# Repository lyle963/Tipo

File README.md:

# Tipo
Plug n Play Braille Keyboard for your smartphone

# What is available?
1. Arduino Firmware for a USB keyboard using atmega32u4
2. Eagle CAD board files to print the PCB

# TO-DO
1. Remove bt ezkey module and get the arduino micro to type stuff onto notepad using 2 or 3 buttons - Done

2. Repeat with USBOTG and make sure phone responds - Done

3. Connect 8 keys to micro on breadboard in matrix or parallel layout to verify all peri electronics - Done

4. Dump Leonardo bootloader to wild Atmega32u4 Chip - Done

5. Breadboard standalone chip with external oscillator,caps,resistors etc - Skipped like a bawz

6. Design / Fab pcb and test with phone - Done

7. CAD Case

8. Print case

9. Give board to visually impared peeps & get feedback

10. Brailler Trainer app

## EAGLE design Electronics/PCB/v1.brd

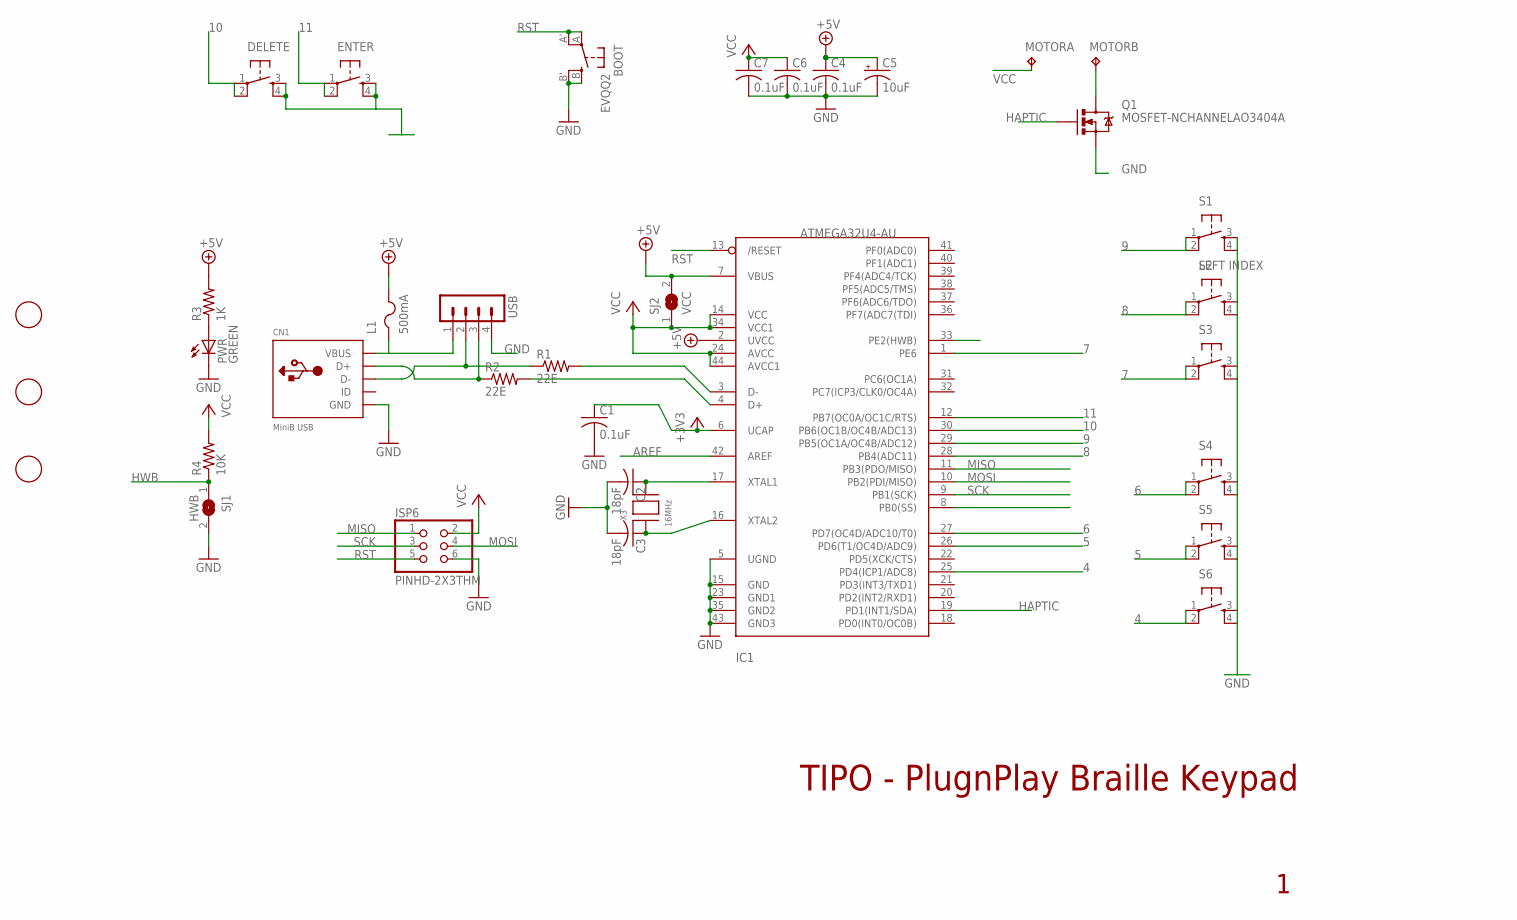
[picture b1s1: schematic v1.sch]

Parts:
BOOT: EVQQ2; EVQ-Q2
C1, C4, C6, C7: 0.1uF; C0805K
C2, C3: 18pF; C0805K
C5: 10uF; A/3216-18R
CN1: MiniB USB; USB-MINIB
DELETE: TAC_SWITCHPTH; TACTILE-PTH
ENTER: TAC_SWITCHPTH; TACTILE-PTH
IC1: ATMEGA32U4-AU; TQFP44
ISP6: PINHD-2X3THM; ISP6
L1: 500mA; R1206
MOTOR: TP2P2-38-17; P2-38-17
PWR: GREEN; CHIPLED_0805
Q1: MOSFET-NCHANNELAO3404A; SOT23-3
R1, R2: 22E; R0805
R3: 1K; R0805
R4: 10K; R0805
S1: LEFT INDEX; TACTILE-PTH
S2, S3, S4, S5, S6: TAC_SWITCHPTH; TACTILE-PTH
SJ1: HWB; SJ
SJ2: VCC; SJ
U$1, U$2, U$6: FIDUCIAL; FIDUCIAL_1MM
USB: MA04-1
X3: 16MHz; NX5032

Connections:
4: IC1.25 (PD4(ICP1/ADC8)), S6.1, S6.2
5: IC1.26 (PD6(T1/OC4D/ADC9)), S5.1, S5.2
6: IC1.27 (PD7(OC4D/ADC10/T0)), S4.1, S4.2
7: IC1.1 (PE6), S3.1, S3.2
8: IC1.28 (PB4(ADC11)), S2.1, S2.2
9: IC1.29 (PB5(OC1A/OC4B/ADC12)), S1.1, S1.2
10: DELETE.1, DELETE.2, IC1.30 (PB6(OC1B/OC4B/ADC13))
11: ENTER.1, ENTER.2, IC1.12 (PB7(OC0A/OC1C/RTS))
+3V3: C1.1, IC1.6 (UCAP)
+5V: C4.1, C5.+, IC1.2 (UVCC), IC1.7 (VBUS), L1.2, R3.2, SJ2.2
AREF: IC1.42 (AREF)
GND: BOOT.B (S), BOOT.B' (S1), C1.2, C2.2, C3.2, C4.2, C5.-, C6.2, C7.2, CN1.GND, DELETE.3, DELETE.4, ENTER.3, ENTER.4, IC1.5 (UGND), IC1.15 (GND), IC1.23 (GND1), IC1.35 (GND2), IC1.43 (GND3), ISP6.6, PWR.C, Q1.2 (S), S1.3, S1.4, S2.3, S2.4, S3.3, S3.4, S4.3, S4.4, S5.3, S5.4, S6.3, S6.4, SJ1.2, USB.4
HAPTIC: IC1.19 (PD1(INT1/SDA)), Q1.1 (G)
HWB: IC1.33 (PE2(HWB)), R4.1, SJ1.1
MISO: IC1.11 (PB3(PDO/MISO)), ISP6.1
MOSI: IC1.10 (PB2(PDI/MISO)), ISP6.4
unnamed: PWR.A, R3.1
unnamed: CN1.D+, R2.1, USB.3
unnamed: IC1.3 (D-), R1.2
unnamed: IC1.4 (D+), R2.2
unnamed: CN1.D-, R1.1, USB.2
unnamed: MOTOR.TP-2, Q1.3 (D)
unnamed: C2.1, IC1.17 (XTAL1), X3.P$2
unnamed: C3.1, IC1.16 (XTAL2), X3.P$1
PB0: IC1.8 (PB0(SS))
RST: BOOT.A, BOOT.A' (P1), IC1.13 (/RESET), ISP6.5
SCK: IC1.9 (PB1(SCK)), ISP6.3
VBUS: CN1.VBUS, L1.1, USB.1
VCC: C6.1, C7.1, IC1.14 (VCC), IC1.24 (AVCC), IC1.34 (VCC1), IC1.44 (AVCC1), ISP6.2, MOTOR.TP-1, R4.2, SJ2.1

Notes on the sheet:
TIPO - PlugnPlay Braille Keypad

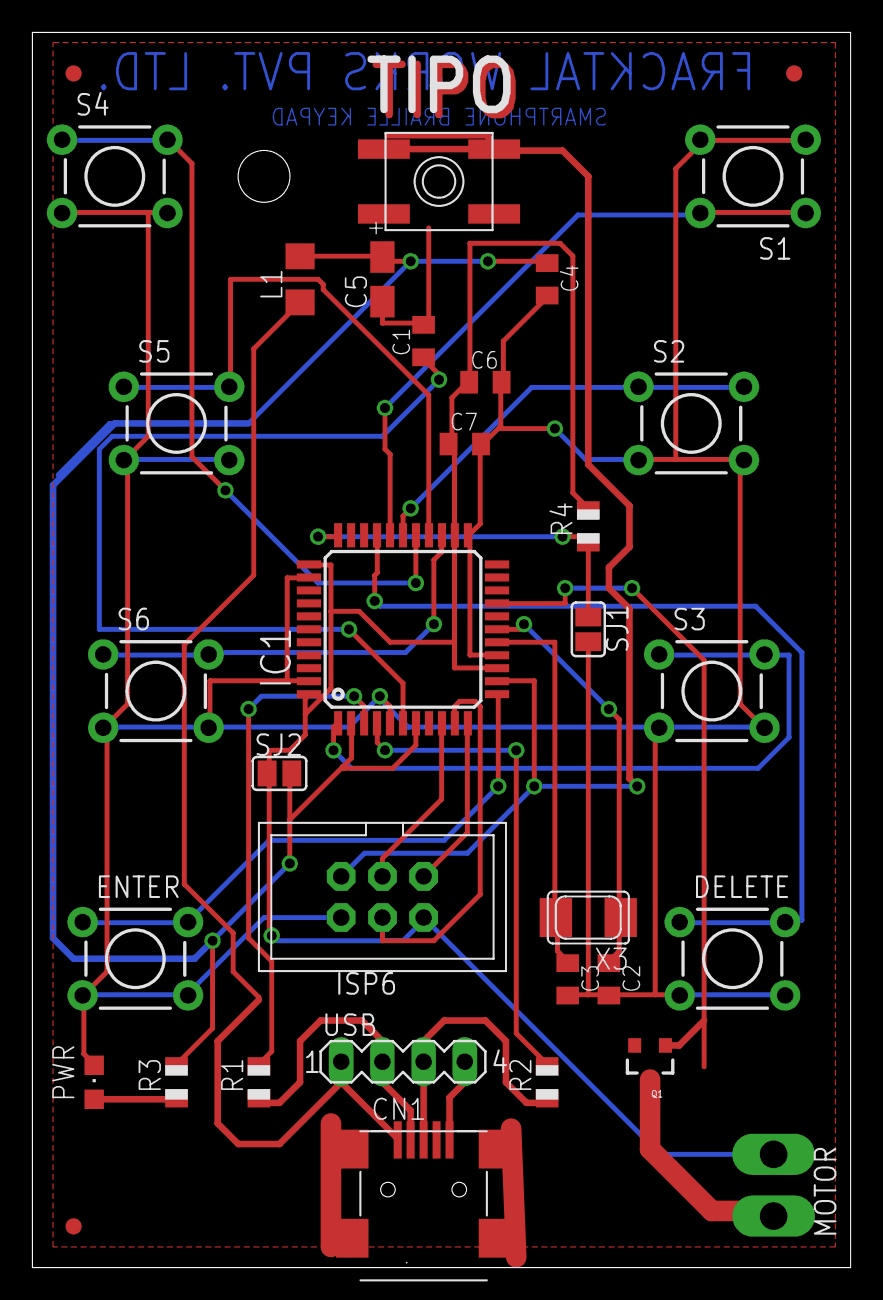
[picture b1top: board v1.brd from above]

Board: 2 copper layers, 50.5 x 76.2 mm, 34 parts (0 on the bottom side), 27 nets.

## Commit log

2017-05-14 Braille v1 - Tested
2017-05-14 Space bar working
2017-05-14 Rename Codes.ino to kboard.ino
2017-05-14 Cleanup
2017-05-14 Rename kboard.ino to Firmware/code/kboard.ino
2017-05-14 Rename Braille.ino to Firmware/code/Braille.ino

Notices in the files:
parts and their libraries:
SparkFun-Retired: Licensing:Creative Commons ShareAlike 4.0 International - https://creativecommons.org/licenses/by-sa/4.0
